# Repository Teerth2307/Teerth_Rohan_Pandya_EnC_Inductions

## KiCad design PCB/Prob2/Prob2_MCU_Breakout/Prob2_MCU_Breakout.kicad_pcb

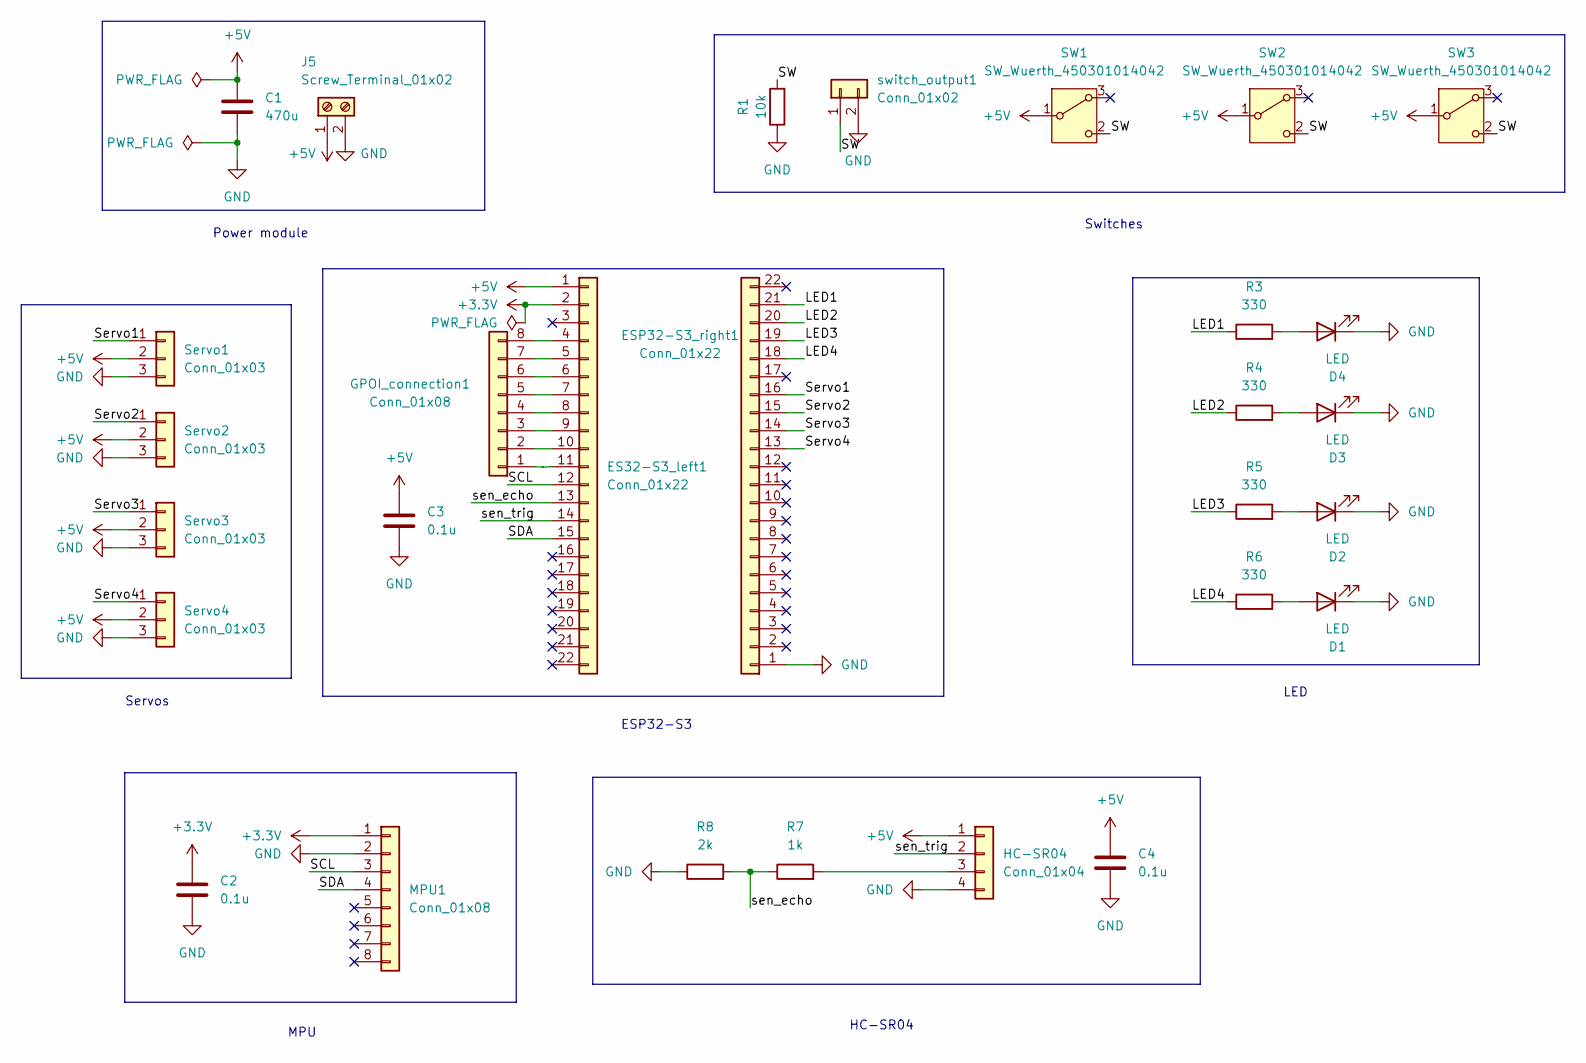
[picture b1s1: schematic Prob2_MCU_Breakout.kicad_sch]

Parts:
C1: 470u; C_Radial_D6.3mm_H7.0mm_P2.50mm
C2, C3, C4: 0.1u; C_0201_0603Metric_Pad0.64x0.40mm_HandSolder
D1, D2, D3, D4: LED; LED_0201_0603Metric
ES32-S3_left1: Conn_01x22; PinSocket_1x22_P2.54mm_Vertical
ESP32-S3_right1: Conn_01x22; PinSocket_1x22_P2.54mm_Vertical
GPOI_connection1: Conn_01x08; PinHeader_1x08_P2.54mm_Vertical
HC-SR04: Conn_01x04; PinSocket_1x04_P2.54mm_Vertical
J5: Screw_Terminal_01x02; TerminalBlock_Phoenix_MKDS-1,5-2-5.08_1x02_P5.08mm_Horizont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
MPU1: Conn_01x08; MPU_6050_foot
R1: 10k; R_Axial_DIN0204_L3.6mm_D1.6mm_P5.08mm_Horizontal
R3, R4, R5, R6: 330; R_0201_0603Metric
R7: 1k; R_0402_1005Metric
R8: 2k; R_0402_1005Metric
SW1, SW2, SW3: SW_Wuerth_450301014042; SW_Slide-03_Wuerth-WS-SLTV_10x2.5x6.4_P2.54mm
Servo1, Servo2, Servo3, Servo4: Conn_01x03; PinHeader_1x03_P2.54mm_Vertical
switch_output1: Conn_01x02; PinHeader_1x02_P2.54mm_Vertical

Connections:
+3.3V: C2.1, ES32-S3_left1.2, MPU1.1
+5V: C1.1, C3.1, C4.1, ES32-S3_left1.1, HC-SR04.1, J5.1, SW1.1 (B), SW2.1 (B), SW3.1 (B), Servo1.2, Servo2.2, Servo3.2, Servo4.2
/LED1: ESP32-S3_right1.21, R3.1
/LED2: ESP32-S3_right1.20, R4.1
/LED3: ESP32-S3_right1.19, R5.1
/LED4: ESP32-S3_right1.18, R6.1
/SCL: ES32-S3_left1.12, MPU1.3
/SDA: ES32-S3_left1.15, MPU1.4
/SW: R1.2, SW1.2 (C), SW2.2 (C), SW3.2 (C), switch_output1.1
/Servo1: ESP32-S3_right1.16, Servo1.1
/Servo2: ESP32-S3_right1.15, Servo2.1
/Servo3: ESP32-S3_right1.14, Servo3.1
/Servo4: ESP32-S3_right1.13, Servo4.1
/sen_echo: ES32-S3_left1.13, R7.1, R8.2
/sen_trig: ES32-S3_left1.14, HC-SR04.2
GND: C1.2, C2.2, C3.2, C4.2, D1.1 (K), D2.1 (K), D3.1 (K), D4.1 (K), ESP32-S3_right1.1, HC-SR04.4, J5.2, MPU1.2, R1.1, R8.1, Servo1.3, Servo2.3, Servo3.3, Servo4.3, switch_output1.2
unnamed: D1.2 (A), R6.2
unnamed: D2.2 (A), R5.2
unnamed: D3.2 (A), R4.2
unnamed: D4.2 (A), R3.2
unnamed: ES32-S3_left1.4, GPOI_connection1.8
unnamed: ES32-S3_left1.5, GPOI_connection1.7
unnamed: ES32-S3_left1.6, GPOI_connection1.6
unnamed: ES32-S3_left1.7, GPOI_connection1.5
unnamed: ES32-S3_left1.8, GPOI_connection1.4
unnamed: ES32-S3_left1.9, GPOI_connection1.3
unnamed: ES32-S3_left1.10, GPOI_connection1.2
unnamed: ES32-S3_left1.11, GPOI_connection1.1
unnamed: HC-SR04.3, R7.2

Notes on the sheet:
Power module
Switches
Servos
LED
ESP32-S3
HC-SR04
MPU

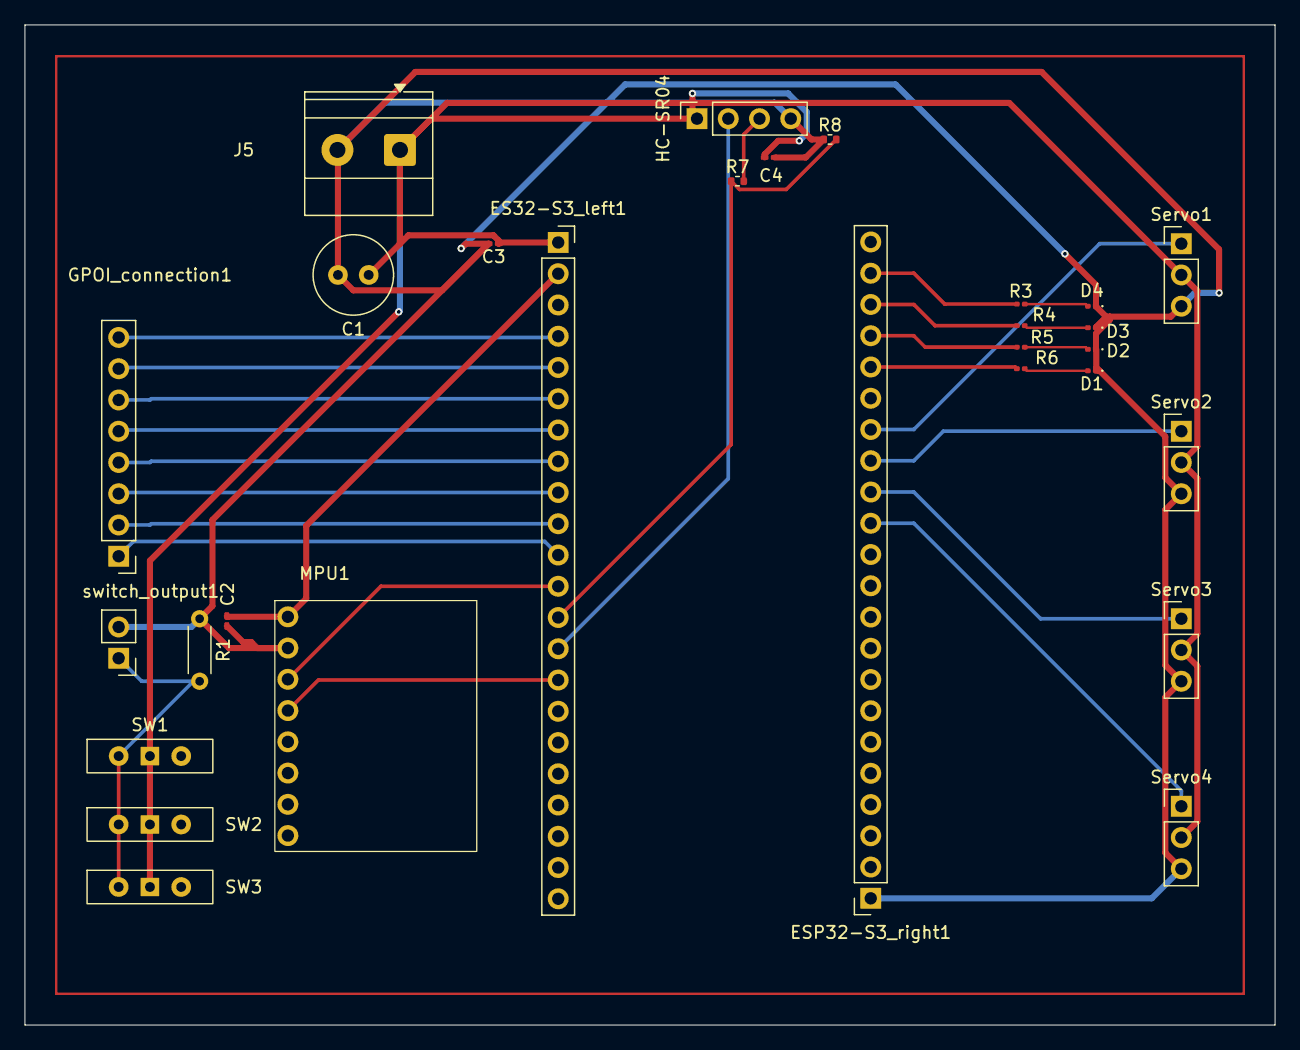
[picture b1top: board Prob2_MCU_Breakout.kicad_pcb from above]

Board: 2 copper layers, 101.6 x 81.3 mm, 29 parts (0 on the bottom side), 29 nets.

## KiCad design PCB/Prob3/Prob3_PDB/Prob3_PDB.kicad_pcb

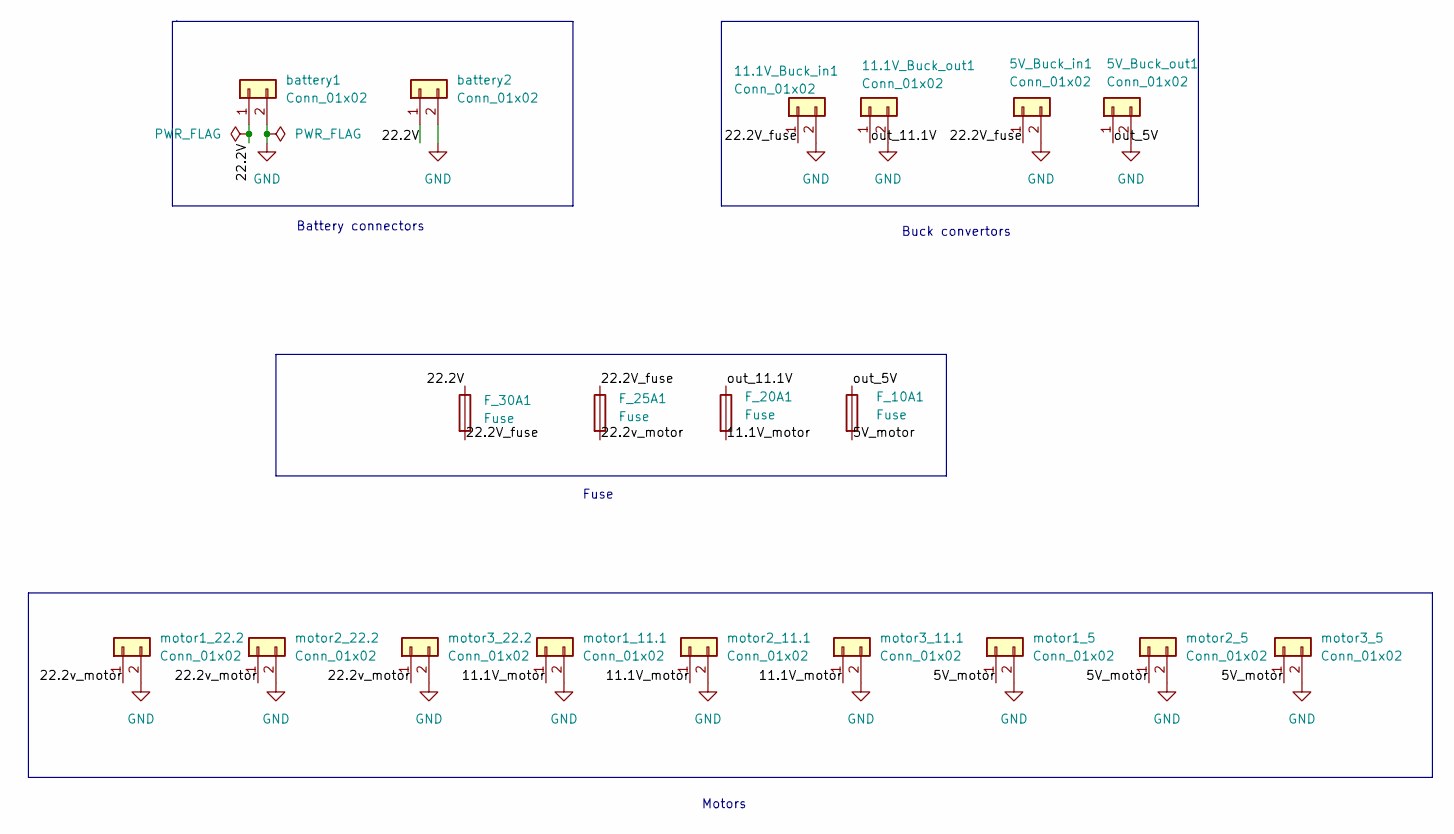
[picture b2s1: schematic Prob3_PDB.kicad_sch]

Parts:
5V_Buck_in1, 5V_Buck_out1, 11.1V_Buck_in1, 11.1V_Buck_out1: Conn_01x02; AMASS_XT60-M_1x02_P7.20mm_Vertical
F_10A1, F_20A1, F_25A1, F_30A1: Fuse; Fuse_Blade_ATO_directSolder
battery1, battery2: Conn_01x02; AMASS_XT60-M_1x02_P7.20mm_Vertical
motor1_5, motor2_5, motor3_5: Conn_01x02; TerminalBlock_Phoenix_MKDS-1,5-2-5.08_1x02_P5.08mm_Horizont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
motor1_11.1, motor2_11.1, motor3_11.1: Conn_01x02; AMASS_XT60-F_1x02_P7.20mm_Vertical
motor1_22.2, motor2_22.2, motor3_22.2: Conn_01x02; AMASS_XT60-M_1x02_P7.20mm_Vertical

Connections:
/5V_motor: F_10A1.2, motor1_5.1, motor2_5.1, motor3_5.1
/11.1V_motor: F_20A1.2, motor1_11.1.1, motor2_11.1.1, motor3_11.1.1
/22.2V: F_30A1.1, battery1.1, battery2.1
/22.2V_fuse: 5V_Buck_in1.1, 11.1V_Buck_in1.1, F_25A1.1, F_30A1.2
/22.2v_motor: F_25A1.2, motor1_22.2.1, motor2_22.2.1, motor3_22.2.1
/out_5V: 5V_Buck_out1.1, F_10A1.1
/out_11.1V: 11.1V_Buck_out1.1, F_20A1.1
GND: 5V_Buck_in1.2, 5V_Buck_out1.2, 11.1V_Buck_in1.2, 11.1V_Buck_out1.2, battery1.2, battery2.2, motor1_5.2, motor1_11.1.2, motor1_22.2.2, motor2_5.2, motor2_11.1.2, motor2_22.2.2, motor3_5.2, motor3_11.1.2, motor3_22.2.2

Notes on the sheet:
Motors
Buck convertors
Battery connectors
Fuse

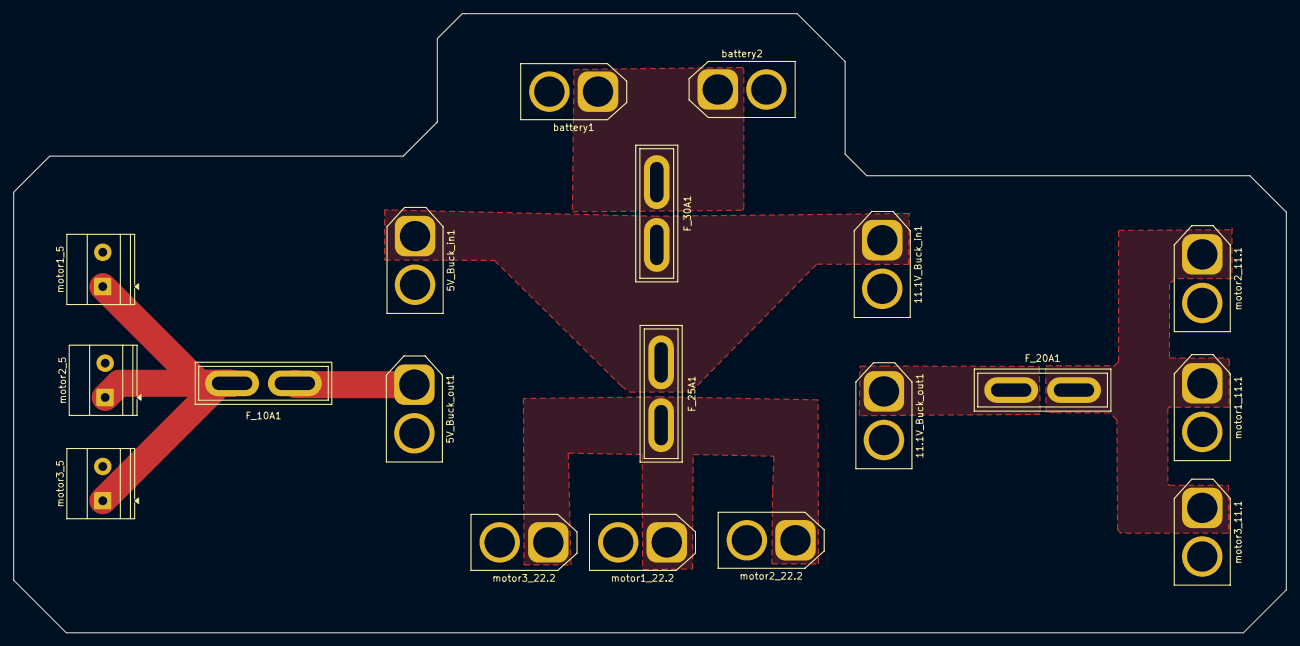
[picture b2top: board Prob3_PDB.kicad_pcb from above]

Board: 2 copper layers, 188.5 x 91.7 mm, 19 parts (0 on the bottom side), 8 nets.
